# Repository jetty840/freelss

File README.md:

#FreeLSS

FreeLSS is a laser scanning program for the Raspberry Pi. It allows a Raspberry Pi to function as the core to a complete turn table laser scanning system.

###THIS FORK

This fork adds Neopixel ring support to freelss.  It includes the circuit/board design for a small mainly SMD shield to handle Neopixels / lasers and steppers.

The advantage of the Neopixel ring is adjustable color and brightness for illumination of the object and reporting of the ip address at startup (useful in DHCP configs).

If you are not usng Neopixels, you can still use the board and omit a few components if you require a small form factor, or use a different board.

Additionally, custom PWM (White) lighting can be setup such that the model and lasers can have different ambient lighting.

###COMPILE

These instructions assume you are running the latest version of Raspbian.  Other distros will likely require changes.

First, update the firmware to the latest version and reboot.
```
$ sudo apt-get update
$ sudo apt-get upgrade
```

Install the dependencies that are managed by the package manager.
```
$ sudo apt-get install libpng-dev libjpeg-dev cmake vlc git-core gcc build-essential unzip sqlite3 libsqlite3-dev libmicrohttpd-dev libcurl4-openssl-dev libiw-dev libssl-dev
```

Download and install wiringPi
```
$ git clone git://git.drogon.net/wiringPi
$ cd wiringPi
$ ./build
$ cd ..
```

Disable the soundcard on the Pi (interferes with Neopixels):
Reference: http://www.instructables.com/id/Disable-the-Built-in-Sound-Card-of-Raspberry-Pi/
```
$ cd /etc/modprobe.d
$ sudo vi alsa-blacklist.conf
Add the following line:
  blacklist snd_bcm2835
Save
$ sudo reboot

After reboot:
$ aplay -l
  Should say "No soundcards found"

```

Download and install rpi_ws821x
Reference: https://learn.adafruit.com/neopixels-on-raspberry-pi/software
```
$ sudo apt-get install build-essential python-dev git scone swig
$ git clone https://github.com/jgarff/rpi_ws281x.git
$ cd rpi_ws281x
$ scons
$ sudo ./test
(Neopixels will go through color cycling, press CTRL-C when done)
$ cd ..
```

Download and build FreeLSS
```
$ git clone https://github.com/jetty840/freelss
$ cd freelss/src
$ make
```
###Running FreeLSS
FreeLSS must be ran as root (or another user with access to the hardware pins).  The interface for FreeLSS is web based and by default runs on port 80.  When running, access it by navigating to http://localhost/ from the Raspberry Pi itself. Or access it from another machine on the network by the Raspberry Pi's IP or hostname.  For Example: http://raspberrypi/

The following command starts FreeLSS.
```
$ sudo ./freelss
```

The following command automatically starts FreeLSS everytime the Raspberry Pi is powered on.
```
$ make startup
```

###Pin Configuraton
For FreeLSS running with the provided schematic/PCB in this fork, configuration for this board is as follows:
```
Right Laser Pin: 4
Left Laser Pin: 0
Laser On Value: 1
Motor Enable Pin: 5
Motor Step Pin: 2
Motor Step Delay: 5000
Motor Direction Pin: 3
Motor Response Delay: 2
Enable Lighting: Checked
Light Type: WS281x
Lighting Pin: 18
```

###Building the board
Populate R4/R6 OR D1/D2, depending on your laser diodes.  If it's 5V and can control it's own current, then populate R4/R6 with a zero ohm resistor.  Otherwise to get the correct voltage for the laser diode, D1/D2 can be used as a Diode drop, and the trace from the middle of the diode pair to +5V can be cut and used as 2 diode drops if required.  Alternative R4/R6 can be used to limit voltage/current less accurately.

For the PI header, decide if you want to use it as a shield (use a PI Stacking Header), or wire 0.1" pin headers if you wish to cable it out (verify pin 1 = pin 1 if you're using IDC headers and a cable).

Adafruit 12 LED Neopixel ring recommended (720ma).  Be careful of current here, the Pi needs to be able to handle it, or supply power using a different method.

2A Minimum 5V PSU required.

DISCLAIMER: By using this design and/or fork, you acknowledge that you do so entirely at your own risk and that you will not hold the author liable under any cicrumstances.

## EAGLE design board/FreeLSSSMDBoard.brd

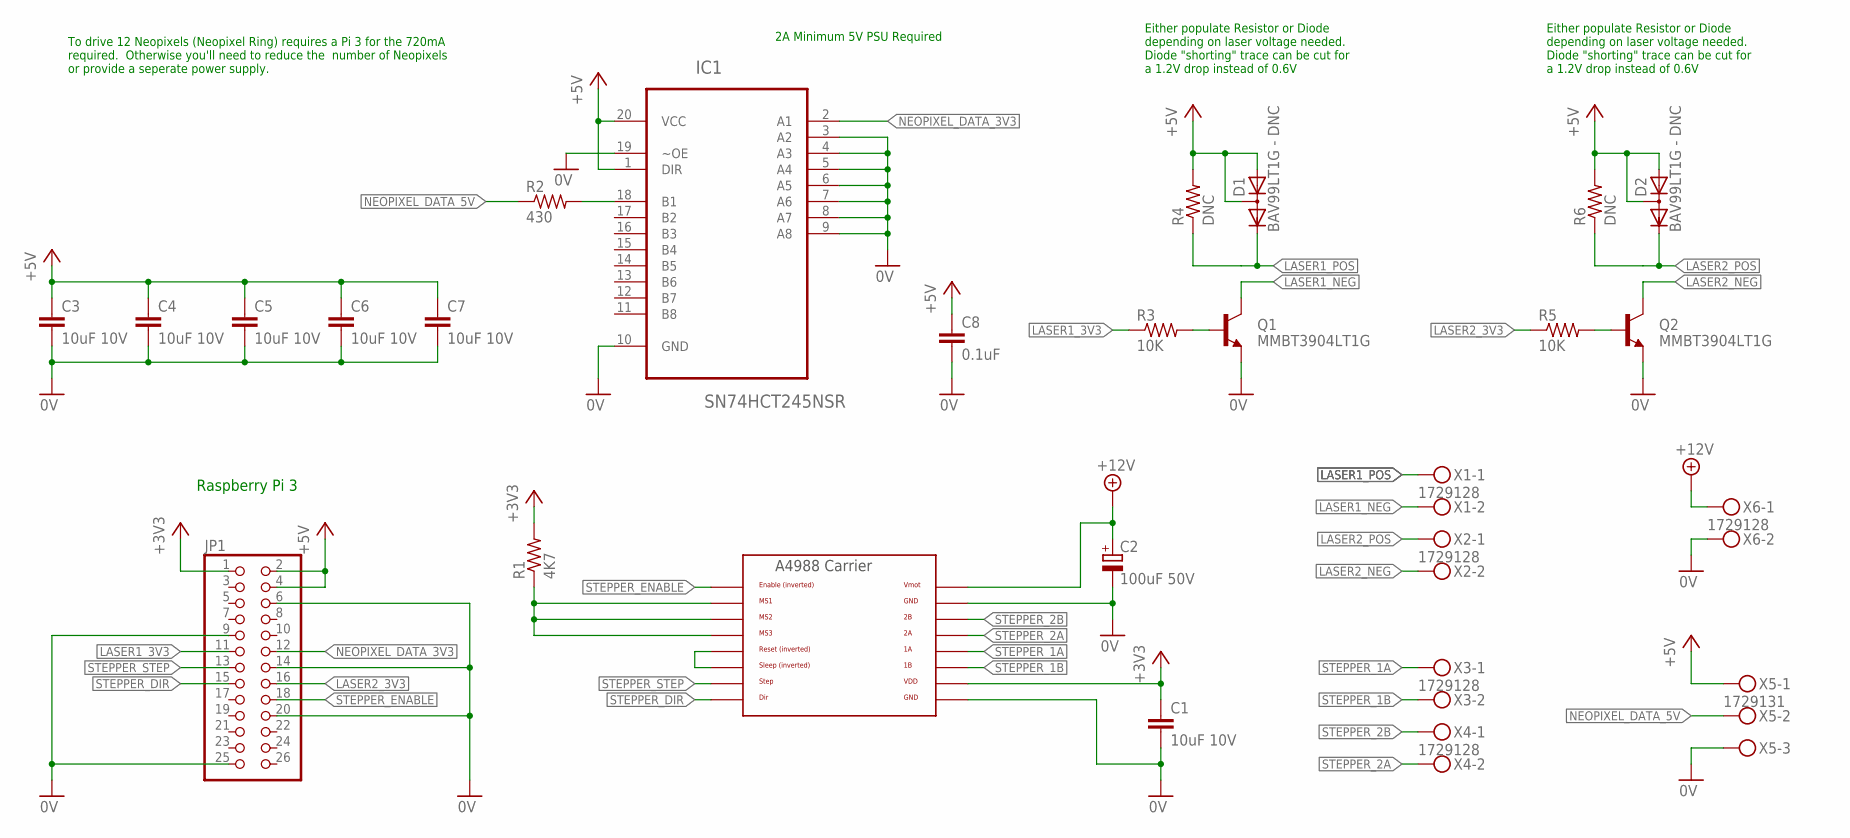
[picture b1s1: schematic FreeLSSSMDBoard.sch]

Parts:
C1, C3, C4, C5, C6, C7: 10uF 10V; C0603K
C2: 100uF 50V; E3,5-8
C8: 0.1uF; C0603K
D1, D2: BAV99LT1G - DNC; SOT23
IC1: SN74HCT245NSR; SOP-20
JP1: PINHD-2X13; 2X13
Q1, Q2: MMBT3904LT1G; SOT23-BEC
R1: 4K7; R0603
R2: 430; R0603
R3, R5: 10K; R0603
R4, R6: DNC; R0603
U$1: A4988BREAKOUT
X1, X2, X3, X4, X6: 1729128; MKDSN1,5/2-5,08
X5: 1729131; MKDSN1,5/3-5,08

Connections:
0V: C1.2, C2.-, C3.2, C4.2, C5.2, C6.2, C7.2, C8.2, IC1.3 (A2), IC1.4 (A3), IC1.5 (A4), IC1.6 (A5), IC1.7 (A6), IC1.8 (A7), IC1.9 (A8), IC1.10 (GND), IC1.19 (~OE), JP1.6, JP1.9, JP1.14, JP1.20, JP1.25, Q1.E, Q2.E, U$1.GND, U$1.GND@0 (GND), X5.3, X6.2
+3V3: C1.1, JP1.1, R1.2, U$1.VDD
+5V: C3.1, C4.1, C5.1, C6.1, C7.1, C8.1, D1.1 (A), D1.3 (AC), D2.1 (A), D2.3 (AC), IC1.1 (DIR), IC1.20 (VCC), JP1.2, JP1.4, R4.2, R6.2, X5.1
+12V: C2.+, U$1.VMOT, X6.1
LASER1_3V3: JP1.11, R3.1
LASER1_NEG: Q1.C, X1.2
LASER1_POS: D1.2 (C), R4.1, X1.1
LASER2_3V3: JP1.16, R5.1
LASER2_NEG: Q2.C, X2.2
LASER2_POS: D2.2 (C), R6.1, X2.1
unnamed: U$1.RST, U$1.SLP (SLEEP)
unnamed: R1.1, U$1.MS1, U$1.MS2, U$1.MS3
unnamed: IC1.18 (B1), R2.2
unnamed: Q1.B, R3.2
unnamed: Q2.B, R5.2
NEOPIXEL_DATA_3V3: IC1.2 (A1), JP1.12
NEOPIXEL_DATA_5V: R2.1, X5.2
STEPPER_1A: U$1.1A, X3.1
STEPPER_1B: U$1.1B, X3.2
STEPPER_2A: U$1.2A, X4.2
STEPPER_2B: U$1.2B, X4.1
STEPPER_DIR: JP1.15, U$1.DIR
STEPPER_ENABLE: JP1.18, U$1.EN
STEPPER_STEP: JP1.13, U$1.STEP

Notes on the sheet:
Raspberry Pi 3
Either populate Resistor or Diode depending on laser voltage needed. Diode "shorting" trace can be cut for a 1.2V drop instead of 0.6V
To drive 12 Neopixels (Neopixel Ring) requires a Pi 3 for the 720mA required. Otherwise you'll need to reduce the number of Neopixels or provide a seperate power supply.
2A Minimum 5V PSU Required

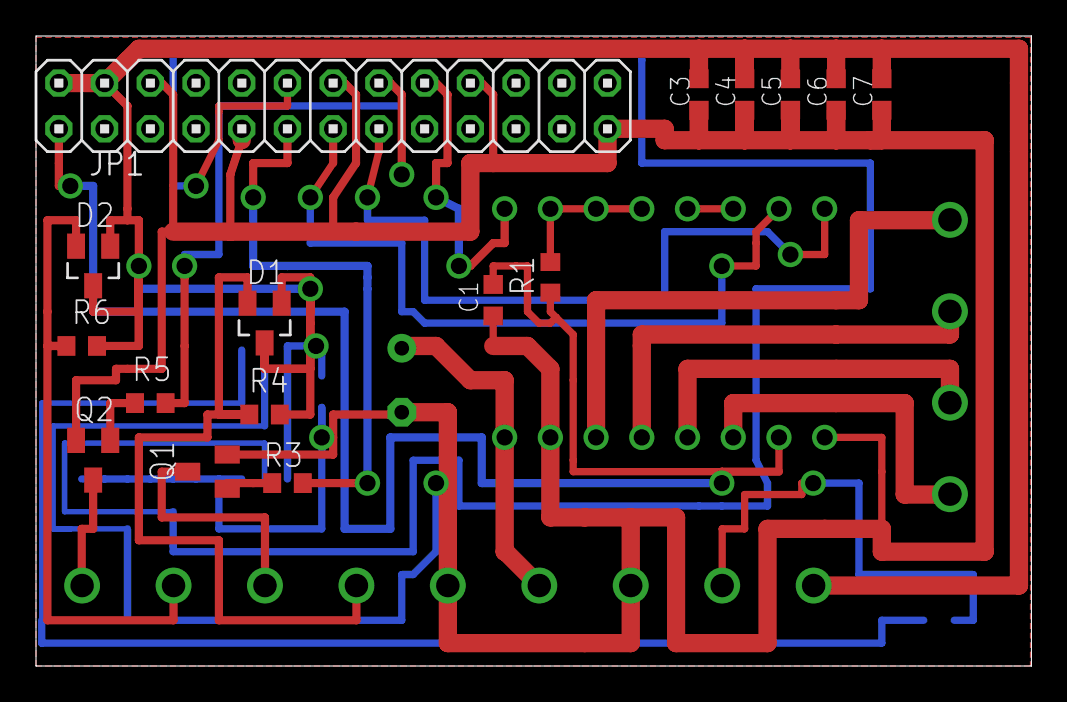
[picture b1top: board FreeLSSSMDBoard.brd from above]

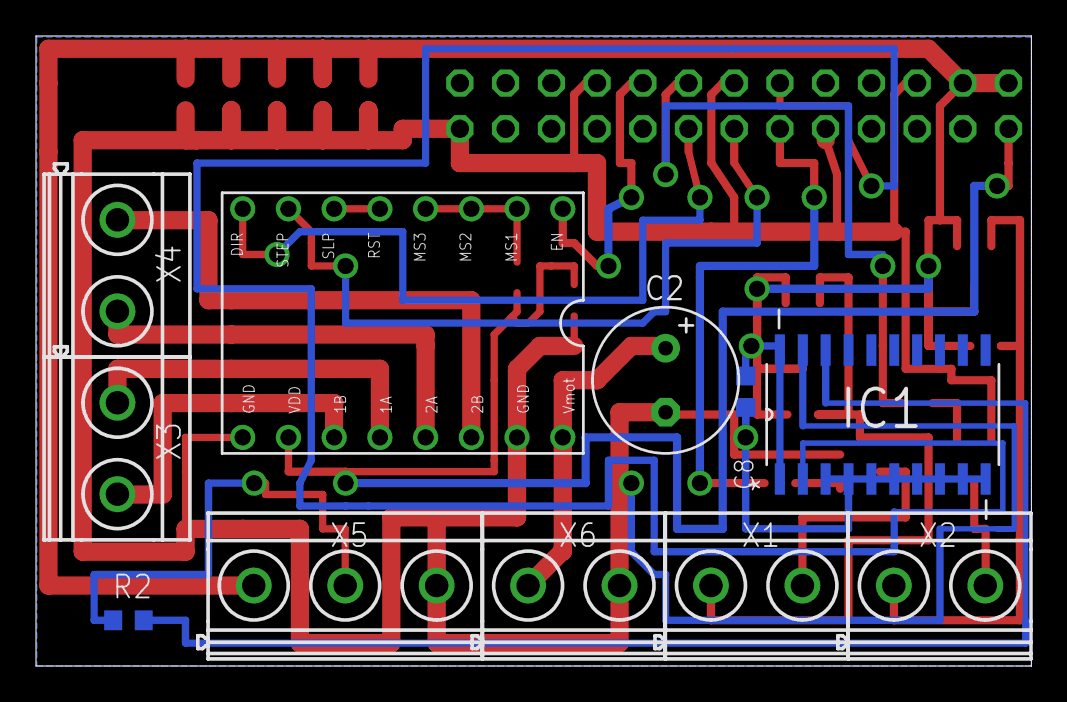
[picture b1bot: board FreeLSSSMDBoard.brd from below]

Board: 2 copper layers, 55.3 x 35.0 mm, 27 parts (11 on the bottom side), 24 nets.

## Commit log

2016-07-04 Initial version, interimZ
2016-07-04 Lighting implementation completed
2016-07-06 Added ip reporting, tested working on Pi 3 with 12 Pixel Neopixel Ring and included board.
2016-07-06 Added boards
